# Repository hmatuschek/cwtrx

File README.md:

# Multiband QRP CW TRX based on the QCX

This repository contains all CAD files for the PCBs, documentation and 
firmware sourcecode for my small [portable multi-band QRP CW transceiver](https://dm3mat.darc.de/cw2019). 

## License
This work is licensed under a [Creative Commons Attribution-ShareAlike 4.0 International License](http://creativecommons.org/licenses/by-sa/4.0/).

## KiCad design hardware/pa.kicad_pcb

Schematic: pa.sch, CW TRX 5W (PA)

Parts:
C1, C10, C19, C23, C27, C29, C30: 100n; C_Disc_D3.0mm_W2.0mm_P2.50mm
C2: 100p; C_Disc_D3.0mm_W1.6mm_P2.50mm
C3, C16: 220p; C_Disc_D3.0mm_W2.0mm_P2.50mm
C4, C7, C17: 470p; C_Disc_D3.0mm_W2.0mm_P2.50mm
C5, C18: 820p; C_Disc_D3.0mm_W2.0mm_P2.50mm
C6, C11: 220p; C_Disc_D3.0mm_W1.6mm_P2.50mm
C8: 1n; C_Disc_D3.0mm_W2.0mm_P2.50mm
C9: 1.5n; C_Disc_D3.0mm_W2.0mm_P2.50mm
C12: 470p; C_Disc_D3.0mm_W1.6mm_P2.50mm
C13: 1n; C_Disc_D3.0mm_W1.6mm_P2.50mm
C14: 1.5n; C_Disc_D3.0mm_W1.6mm_P2.50mm
C15: 100p; C_Disc_D3.0mm_W2.0mm_P2.50mm
C20, C22, C24, C31: 100n; C_Disc_D4.7mm_W2.5mm_P5.00mm
C21: 1n; C_Disc_D4.3mm_W1.9mm_P5.00mm
C25: 1u; C_Disc_D4.3mm_W1.9mm_P5.00mm
C26: 220u; CP_Radial_D6.3mm_P2.50mm
C28: 100n; C_Disc_D4.3mm_W1.9mm_P5.00mm
D1, D2, D3, D5: 1n4148; D_T-1_P5.08mm_Horizontal
D4: 1N4001; D_DO-15_P2.54mm_Vertical_AnodeUp
D6, D7: 1n4148; D_T-1_P2.54mm_Vertical_AnodeUp
H1, H2, H3, H4: GND; MountingHole_3.2mm_M3_Pad_Via
J1: Conn_Coaxial; BNC_Amphenol_B6252HB-NPP3G-50_Horizontal
J2: FromRX; PinSocket_1x08_P2.54mm_Vertical
J3: Barrel_Jack_Switch; BarrelJack_Wuerth_6941xx301002
J6: RX-HF; PinSocket_1x02_P2.54mm_Vertical
J7: TX-HF; PinSocket_1x02_P2.54mm_Vertical
J11: RXSupply; PinSocket_1x02_P2.54mm_Vertical
K1, K2, K3, K4: G6S-2; Relay_DPDT_Omron_G6S-2
L1, L5: 330n; L_Toroid_Vertical_L10.0mm_W5.0mm_P5.08mm_Diagonal_Rev
L2, L6, L10: 480n; L_Toroid_Vertical_L10.0mm_W5.0mm_P5.08mm_Diagonal
L3, L7: 750n; L_Toroid_Vertical_L10.0mm_W5.0mm_P5.08mm_Diagonal_Rev
L4, L8, L12: 1700n; L_Toroid_Vertical_L10.0mm_W5.0mm_P5.08mm_Diagonal
L9: 330n; L_Toroid_Vertical_L10.0mm_W5.0mm_P5.08mm_Diagonal
L11: 750n; L_Toroid_Vertical_L10.0mm_W5.0mm_P5.08mm_Diagonal
L13: 100u; L_Axial_L7.0mm_D3.3mm_P10.16mm_Horizontal_Fastron_MICC
L14: 22u; L_Radial_D8.7mm_P5.00mm_Fastron_07HCP
Q1, Q2, Q3, Q10: 2N3904; TO-92_Inline_Wide
Q4, Q6, Q7, Q8, Q9, Q11: BS170; TO-92_Inline_Wide
Q5: BD140-16; TO-126-3_Horizontal_TabDown
R1, R3, R5, R11: 10k; R_Axial_DIN0207_L6.3mm_D2.5mm_P2.54mm_Vertical
R2, R4, R6, R8: 100k; R_Axial_DIN0207_L6.3mm_D2.5mm_P2.54mm_Vertical
R7: 10k; R_Axial_DIN0204_L3.6mm_D1.6mm_P7.62mm_Horizontal
R9: 470; R_Axial_DIN0204_L3.6mm_D1.6mm_P5.08mm_Horizontal
R10: 1k; R_Axial_DIN0207_L6.3mm_D2.5mm_P2.54mm_Vertical
R12: 100; R_Axial_DIN0207_L6.3mm_D2.5mm_P7.62mm_Horizontal
R13: 100; R_Axial_DIN0204_L3.6mm_D1.6mm_P5.08mm_Horizontal
R14: 4.7k; R_Axial_DIN0204_L3.6mm_D1.6mm_P5.08mm_Horizontal
R15, R16: 10k; R_Axial_DIN0204_L3.6mm_D1.6mm_P2.54mm_Vertical
T1: 8+8@FT37-43; Transformer_1P_1S_Toroid_Vertical_D10.5mm_Amidon-T37
U1: 74HCT00; DIP-14_W7.62mm_LongPads

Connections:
10m: J2.5, R1.1
20m: J2.6, R3.1
40m: J2.7, R11.1
80m: J2.8, R5.1
+5V: C28.2, J2.1, R14.1, U1.14 (VCC)
+12V: C1.2, C10.2, C19.2, C22.2, C27.2, C29.2, D1.1 (K), D2.1 (K), D3.1 (K), D5.1 (K), K1.1, K2.1, K3.1, K4.1, L13.1, R7.2
GND: C2.2, C3.2, C4.2, C5.2, C6.2, C7.2, C8.2, C9.2, C11.2, C12.2, C13.2, C14.2, C15.2, C16.2, C17.2, C18.2, C22.1, C23.1, C24.1, C26.2, C28.1, C29.1, C30.2, C31.1, D4.2 (A), D6.2 (A), D7.1 (K), H1.1, H2.1, H3.1, H4.1, J1.2 (Ext), J2.2, J3.2, J6.2, J7.2, J11.2, K1.3, K1.10, K2.3, K2.10, K3.3, K3.10, K4.3, K4.10, Q1.1 (E), Q2.1 (E), Q3.1 (E), Q6.3 (S), Q7.3 (S), Q8.3 (S), Q9.3 (S), Q10.1 (E), Q11.3 (S), R2.2, R4.2, R6.2, R8.2, R15.1, R16.1, U1.7 (GND)
KEY5V: J2.4, R13.2
LPF: C20.1, C21.2, K1.5, K2.5, K3.5, K4.5
unnamed: C2.1, K1.9, L1.1
unnamed: C3.1, K2.9, L2.1
unnamed: C4.1, K3.9, L3.1
unnamed: C5.1, K4.9, L4.1
unnamed: C6.1, L1.2, L5.1
unnamed: C7.1, L2.2, L6.1
unnamed: C8.1, L3.2, L7.1
unnamed: C9.1, L4.2, L8.1
unnamed: C11.1, L5.2, L9.1
unnamed: C12.1, L6.2, L10.1
unnamed: C13.1, L7.2, L11.1
unnamed: C14.1, L8.2, L12.1
unnamed: C15.1, K1.4, L9.2
unnamed: C16.1, K2.4, L10.2
unnamed: C17.1, K3.4, L11.2
unnamed: C18.1, K4.4, L12.2
unnamed: C20.2, T1.2 (AB)
unnamed: C21.1, Q4.1 (D), R7.1
unnamed: C23.2, C25.1, Q5.2 (C), T1.4 (SB)
unnamed: C25.2, Q5.3 (B), R9.1, R10.2
unnamed: C26.1, C31.2, L14.1, Q5.1 (E), R9.2
unnamed: C30.1, Q4.2 (G), R12.1, R16.2
unnamed: J1.1 (In), K1.8, K2.8, K3.8, K4.8
unnamed: Q1.2 (B), R1.2, R2.1
unnamed: Q2.2 (B), R3.2, R4.1
unnamed: Q3.2 (B), R5.2, R6.1
unnamed: Q8.1 (D), R10.1
unnamed: Q8.2 (G), R13.1, R15.2
unnamed: Q10.2 (B), R8.1, R11.2
unnamed: Q6.1 (D), Q7.1 (D), Q9.1 (D), Q11.1 (D), T1.1 (AA), T1.3 (SA)
unnamed: Q6.2 (G), Q7.2 (G), Q9.2 (G), Q11.2 (G), U1.3, U1.6
unnamed: U1.1, U1.2, U1.4, U1.5, U1.11
RL10M: C1.1, D1.2 (A), K1.12, Q1.3 (C)
RL20M: C10.1, D2.2 (A), K2.12, Q2.3 (C)
RL40M: C27.1, D5.2 (A), K3.12, Q10.3 (C)
RL80M: C19.1, D3.2 (A), K4.12, Q3.3 (C)
RX5V: R12.2, U1.8
RX-HF: D6.1 (K), D7.2 (A), J6.1, Q4.3 (S)
TX5V: J2.3, U1.9, U1.10, U1.13
TX-HF: J7.1, R14.2, U1.12
VCC: C24.2, D4.1 (K), J3.1, J11.1, L13.2, L14.2

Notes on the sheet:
LP 10m
LP 17m
LP 30m
LP 60m
11T@T37-6
13T@T37-6
14T@T37-2
21T@T37-2

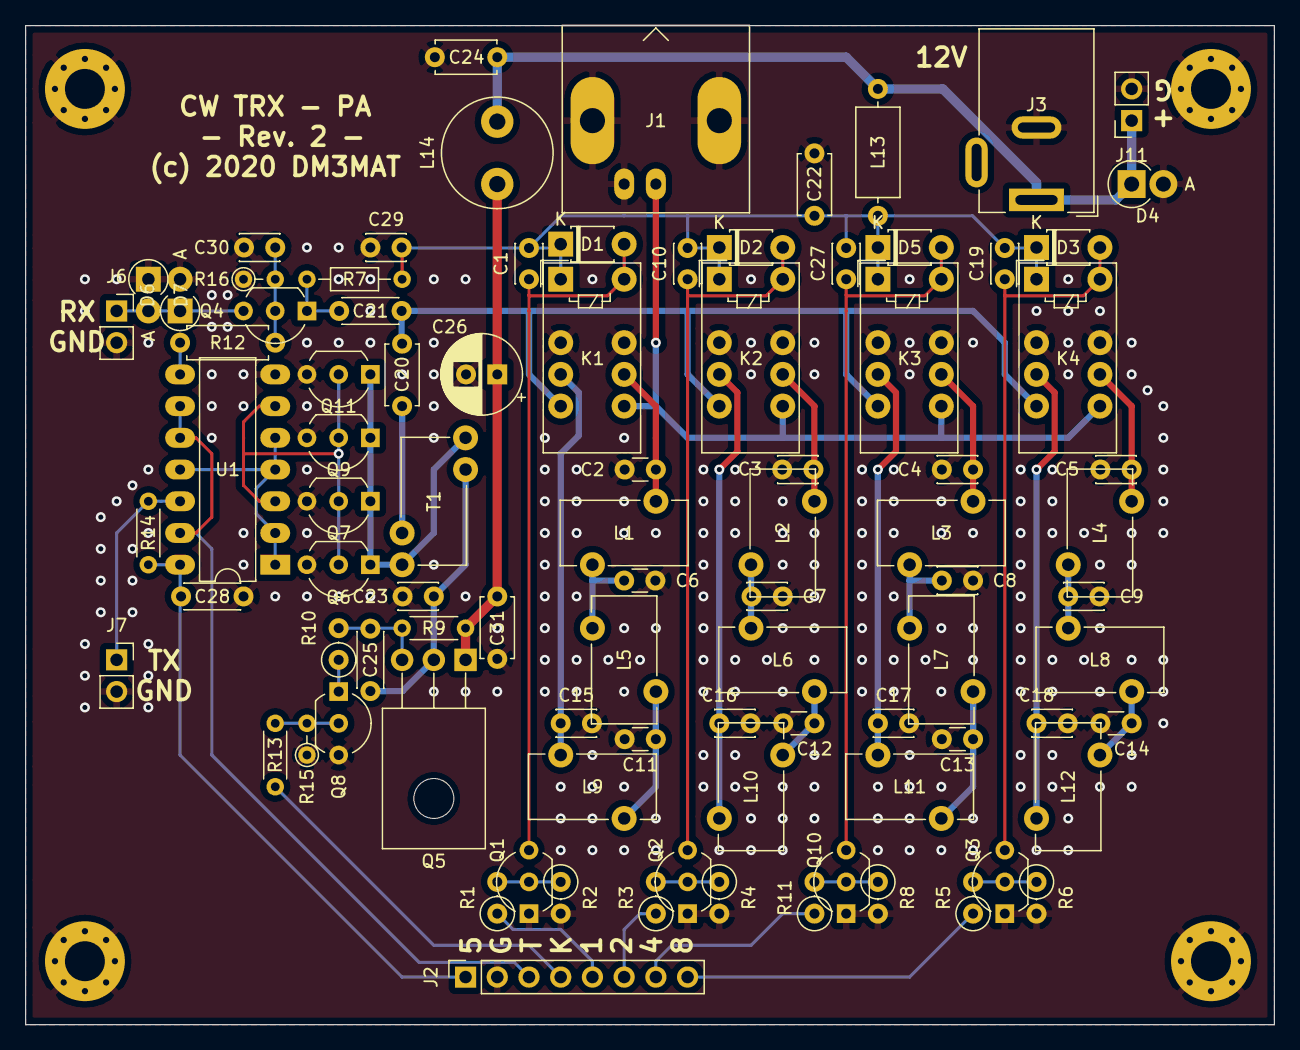
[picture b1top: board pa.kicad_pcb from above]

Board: 2 copper layers, 100.0 x 80.0 mm, 95 parts (0 on the bottom side), 50 nets.

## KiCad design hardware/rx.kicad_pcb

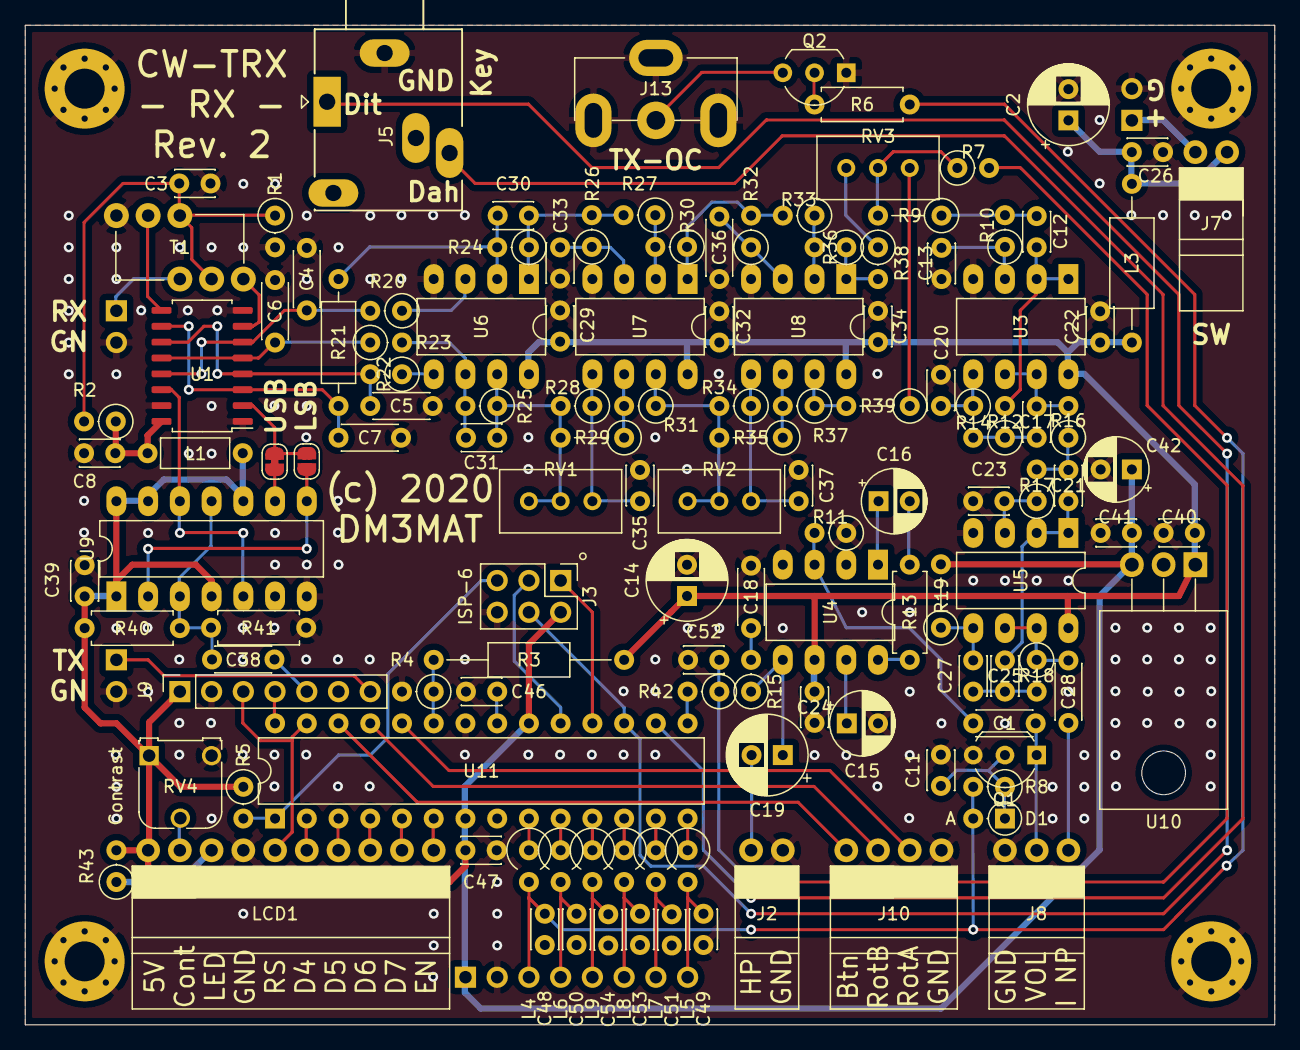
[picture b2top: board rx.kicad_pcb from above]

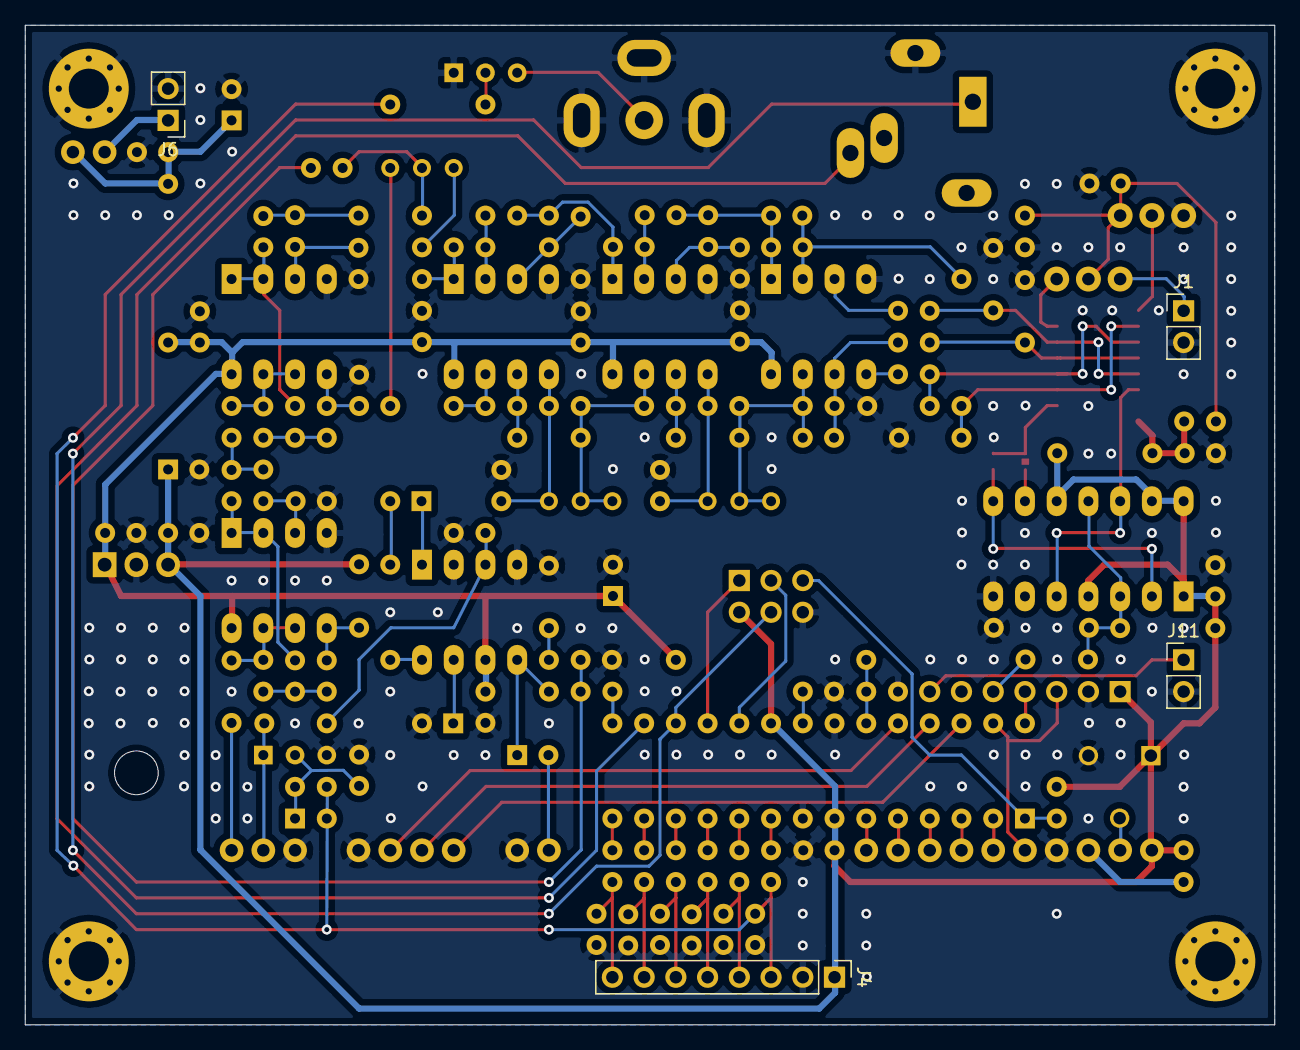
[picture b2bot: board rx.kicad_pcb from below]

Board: 2 copper layers, 100.0 x 80.0 mm, 137 parts (4 on the bottom side), 100 nets.

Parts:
C1, C28: 1u; C_Disc_D4.3mm_W1.9mm_P5.00mm
C2, C14, C19: 100u; CP_Radial_D6.3mm_P2.50mm
C3, C8, C11, C22, C24, C26, C29, C32, C34, C37, C39, C40, C41, C46, C47, C48, C49, C50, C51, C52, C53, C54: 100n; C_Disc_D3.0mm_W2.0mm_P2.50mm
C4, C5, C6, C7, C36: 470n; C_Disc_D4.3mm_W1.9mm_P5.00mm
C12, C17, C21, C33: 47n; C_Disc_D3.0mm_W2.0mm_P2.50mm
C13, C20, C23: 1n; C_Disc_D3.0mm_W2.0mm_P2.50mm
C15, C16, C42: 10u; CP_Radial_D5.0mm_P2.50mm
C18: 47n; C_Disc_D4.3mm_W1.9mm_P5.00mm
C25, C27: 3.3n; C_Disc_D3.0mm_W2.0mm_P2.50mm
C30, C31, C35: 10n; C_Disc_D3.0mm_W2.0mm_P2.50mm
C38: 100n; C_Disc_D4.3mm_W1.9mm_P5.00mm
D1: 1N4148; D_DO-35_SOD27_P2.54mm_Vertical_AnodeUp
H1, H2, H3, H4: GND; MountingHole_3.2mm_M3_Pad_Via
J1: RX-RF; PinHeader_1x02_P2.54mm_Vertical
J2: HP; Connector_BKL_1x02_P2.54mm_Horizontal
J3: AVR-ISP-6; PinHeader_2x03_P2.54mm_Vertical
J4: ToPA; PinHeader_1x08_P2.54mm_Vertical
J5: Key; Jack_3.5mm_Ledino_KB3SPRS_Horizontal
J6: Supply; PinHeader_1x02_P2.54mm_Vertical
J7: SW; Connector_BKL_1x02_P2.54mm_Horizontal
J8: 10K Log; Connector_BKL_1x03_P2.54mm_Horizontal
J9: Si5351; PinSocket_1x07_P2.54mm_Vertical
J10: ROT; Connector_BKL_1x04_P2.54mm_Horizontal
J11: TxOsc; PinHeader_1x02_P2.54mm_Vertical
J13: Conn_Coaxial; RCA_RND_205-00698_Horizontal
JP1: LSB; SolderJumper-2_P1.3mm_Open_RoundedPad1.0x1.5mm
JP2: USB; SolderJumper-2_P1.3mm_Bridged_RoundedPad1.0x1.5mm
L1: 100u; L_Axial_L5.3mm_D2.2mm_P7.62mm_Horizontal_Vishay_IM-1
L3: 100u; L_Axial_L7.0mm_D3.3mm_P12.70mm_Horizontal_Fastron_MICC
L4, L5, L6, L7, L8, L9: 100u; L_Axial_L7.0mm_D3.3mm_P2.54mm_Vertical_Fastron_MICC
LCD1: LCD; Connector_BKL_1x10_P2.54mm_Horizontal
Q1: BS170; TO-92_Inline_Wide
Q2: 2N3904; TO-92_Inline_Wide
R1, R2, R11, R18, R24, R25, R28: 10k; R_Axial_DIN0207_L6.3mm_D2.5mm_P2.54mm_Vertical
R3: 47k; R_Axial_DIN0207_L6.3mm_D2.5mm_P15.24mm_Horizontal
R4: 4.7k; R_Axial_DIN0207_L6.3mm_D2.5mm_P2.54mm_Vertical
R5: 47k; R_Axial_DIN0207_L6.3mm_D2.5mm_P2.54mm_Vertical
R6, R40, R41: 10k; R_Axial_DIN0207_L6.3mm_D2.5mm_P7.62mm_Horizontal
R7, R27, R30, R31, R33, R36, R37: 3.3k; R_Axial_DIN0207_L6.3mm_D2.5mm_P2.54mm_Vertical
R8: 120k; R_Axial_DIN0207_L6.3mm_D2.5mm_P2.54mm_Vertical
R9: 30k; R_Axial_DIN0207_L6.3mm_D2.5mm_P5.08mm_Vertical
R10: 30k; R_Axial_DIN0207_L6.3mm_D2.5mm_P2.54mm_Vertical
R12, R14: 33k; R_Axial_DIN0207_L6.3mm_D2.5mm_P2.54mm_Vertical
R13: 2.2k; R_Axial_DIN0207_L6.3mm_D2.5mm_P7.62mm_Horizontal
R15: 10; R_Axial_DIN0207_L6.3mm_D2.5mm_P2.54mm_Vertical
R16, R17: 36k; R_Axial_DIN0207_L6.3mm_D2.5mm_P2.54mm_Vertical
R19: 470k; R_Axial_DIN0207_L6.3mm_D2.5mm_P5.08mm_Vertical
R20, R22, R23: 100; R_Axial_DIN0207_L6.3mm_D2.5mm_P2.54mm_Vertical
R21: 100; R_Axial_DIN0207_L6.3mm_D2.5mm_P10.16mm_Horizontal
R26: 5.1k; R_Axial_DIN0207_L6.3mm_D2.5mm_P2.54mm_Vertical
R29, R35: 3.3k; R_Axial_DIN0207_L6.3mm_D2.5mm_P5.08mm_Vertical
R32: 4.3k; R_Axial_DIN0207_L6.3mm_D2.5mm_P2.54mm_Vertical
R34: 7.5k; R_Axial_DIN0207_L6.3mm_D2.5mm_P2.54mm_Vertical
R38, R42: 1k; R_Axial_DIN0207_L6.3mm_D2.5mm_P2.54mm_Vertical
R39: 1k; R_Axial_DIN0207_L6.3mm_D2.5mm_P5.08mm_Vertical
R43: 220; R_Axial_DIN0207_L6.3mm_D2.5mm_P2.54mm_Vertical
RV1, RV2: 50k; Potentiometer_Bourns_3296W_Vertical
RV3: 500; Potentiometer_Bourns_3296W_Vertical
RV4: 10k; Potentiometer_Runtron_RM-065_Vertical
T1: 3 x 8 @ FT37-43; Transformer_1P_2S_Toroid_Vertical_D10.5mm_Amidon-T37
U1: FST3253; SOIC-16_4.55x10.3mm_P1.27mm
U3, U5, U6, U7, U8: LM833; DIP-8_W7.62mm_LongPads
U4: LM386; DIP-8_W7.62mm_LongPads
U9: 74HC74; DIP-14_W7.62mm_LongPads
U10: L7805; TO-220-3_Horizontal_TabDown
U11: ATmega328-PU; DIP-28_W7.62mm

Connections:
10M: L9.1, U11.11
20M: L8.1, U11.12
40M: L7.1, U11.13
80M: L5.1, U11.14
+5VA: C8.1, L1.2, R2.1, U1.16
+5VD: C39.2, C41.1, C42.1, C47.1, J3.2, J4.1, J9.1, L1.1, LCD1.1, R5.1, R19.2, R40.2, R43.2, RV4.1, U9.1, U9.4, U9.10, U9.13, U9.14, U10.3, U11.7, U11.20
+12V: C14.1, C22.1, C24.1, C29.1, C32.1, C34.1, C40.1, L3.1, R3.1, U3.8, U4.6, U5.8, U6.8, U7.8, U8.8, U10.1
/Audio/HP: C19.2, J2.1
/Audio/NF: R7.1, R9.2, RV3.2
/Ctrl/10m: C54.2, J4.5, L9.2
/Ctrl/20m: C53.2, J4.6, L8.2
/Ctrl/40m: C51.2, J4.7, L7.2
/Ctrl/80m: C49.2, J4.8, L5.2
/Ctrl/SCL: J9.4, U11.28
/Ctrl/Side: C52.2, R7.2, R42.1
/Demod/I+: C4.1, R20.2, U1.6, U1.13
/Demod/I-: C7.1, R21.2, U1.3, U1.10
/Demod/Q+: C5.1, R22.2, U1.4, U1.11
/Demod/Q-: C6.1, R23.1, U1.5, U1.12
/Mixer/RF: J1.1, T1.2
/Mixer/VFO+I: U1.14, U9.5, U9.12
/Mixer/VFO+Q: JP1.2, JP2.1, U1.2
/VFO/CLK2: C38.2, J9.5
/VFO/VFO+Q: JP2.2, U9.9
/VFO/VFO-Q: JP1.1, U9.2, U9.8
Dah: J5.S, U11.16
Dit: J3.4, J5.T, U11.17
GND: C2.2, C3.2, C4.2, C5.2, C6.2, C7.2, C8.2, C11.2, C13.2, C14.2, C15.2, C18.2, C20.2, C22.2, C23.2, C24.2, C26.2, C29.2, C32.2, C33.2, C34.2, C35.1, C36.2, C37.1, C39.1, C40.2, C41.2, C42.2, C46.1, C47.2, C48.1, C49.1, C50.1, C51.1, C52.1, C53.1, C54.1, H1.1, H2.1, H3.1, H4.1, J1.2, J2.2, J3.6, J4.2, J5.G, J6.2, J8.1, J9.2, J10.4, J11.2, J13.2, LCD1.4, Q1.3, Q2.1, R1.2, R4.2, R11.1, R41.1, RV4.3, T1.1, U1.1, U1.8, U1.15, U3.4, U4.2, U4.4, U5.4, U6.4, U7.4, U8.4, U9.7, U10.2, U11.8, U11.22
KEY: L6.1, U11.10
Key: C50.2, J4.4, L6.2
LCD_CR: LCD1.2, RV4.2
LCD_D4: LCD1.6, U11.2
LCD_D5: LCD1.7, U11.3
LCD_D6: LCD1.8, U11.4
LCD_D7: LCD1.9, U11.5
LCD_EN: LCD1.10, U11.6
LCD_RS: J9.3, LCD1.5, U11.27
MISO: J3.1, U11.18
unnamed: C1.1, R11.2, U4.3
unnamed: C3.1, R1.1, R2.2, T1.4, T1.5
unnamed: C11.1, D1.1, Q1.2, R8.1
unnamed: C12.1, R9.1, R10.2
unnamed: C12.2, R12.2, U3.1, U3.2
unnamed: C13.1, R10.1, U3.3
unnamed: C15.1, U4.7
unnamed: C16.1, U4.1
unnamed: C16.2, R13.2
unnamed: C17.1, R12.1, R14.2
unnamed: C17.2, R16.2, U3.6, U3.7
unnamed: C18.1, R15.2
unnamed: C19.1, R15.1, U4.5
unnamed: C20.1, R14.1, U3.5
unnamed: C21.1, R16.1, R17.2
unnamed: C21.2, C25.1, U5.1, U5.2
unnamed: C23.1, R17.1, U5.3
unnamed: C25.2, C27.1, R18.2
unnamed: C27.2, R19.1, U5.5
unnamed: C28.2, R18.1, U5.6, U5.7
unnamed: C30.1, R24.1, R26.2, R27.2, U6.1
unnamed: C30.2, R21.1, R24.2, U6.2
unnamed: C31.1, R25.1, R28.2, R29.2, RV1.2, RV1.3, U6.7
unnamed: C31.2, R23.2, R25.2, U6.6
unnamed: C33.1, R26.1, U7.3
unnamed: C35.2, R28.1, RV1.1, U7.5
unnamed: C36.1, R32.1, U8.3
unnamed: C37.2, R34.1, RV2.1, U8.5
unnamed: C38.1, R40.1, R41.2, U9.3, U9.11
unnamed: C46.2, U11.21
unnamed: J6.1, J7.1
unnamed: J13.1, Q2.3
unnamed: LCD1.3, R43.1
unnamed: Q2.2, R6.1
unnamed: R13.1, U4.8
unnamed: R20.1, U6.3
unnamed: R22.1, U6.5
unnamed: R27.1, R30.2, U7.2
unnamed: R29.1, R31.2, U7.6
unnamed: R30.1, R32.2, R33.2, U7.1
unnamed: R31.1, R34.2, R35.2, RV2.2, RV2.3, U7.7
unnamed: R33.1, R36.2, U8.2
unnamed: R35.1, R37.2, U8.6
unnamed: R36.1, R38.2, U8.1
unnamed: R37.1, R39.2, U8.7
unnamed: R38.1, RV3.1
unnamed: R39.1, RV3.3
unnamed: T1.3, U1.9
unnamed: T1.6, U1.7
POT-A: C28.1, J8.3
POT-B: C1.2, J8.2, Q1.1
ROT-A: J10.3, U11.24
ROT-B: J10.2, U11.25
ROT-M: J10.1, U11.26
RST: J3.5, R5.2, U11.1
SCK: J3.3, U11.19
SIDE: R42.2, U11.15
TX: L4.1, U11.9
TX5V: C48.2, D1.2, J4.3, L4.2, R6.2, R8.2
TX-OSC: J9.7, J11.1
VCC: C2.1, C26.1, J7.2, L3.2
Vbat: R3.2, R4.1, U11.23

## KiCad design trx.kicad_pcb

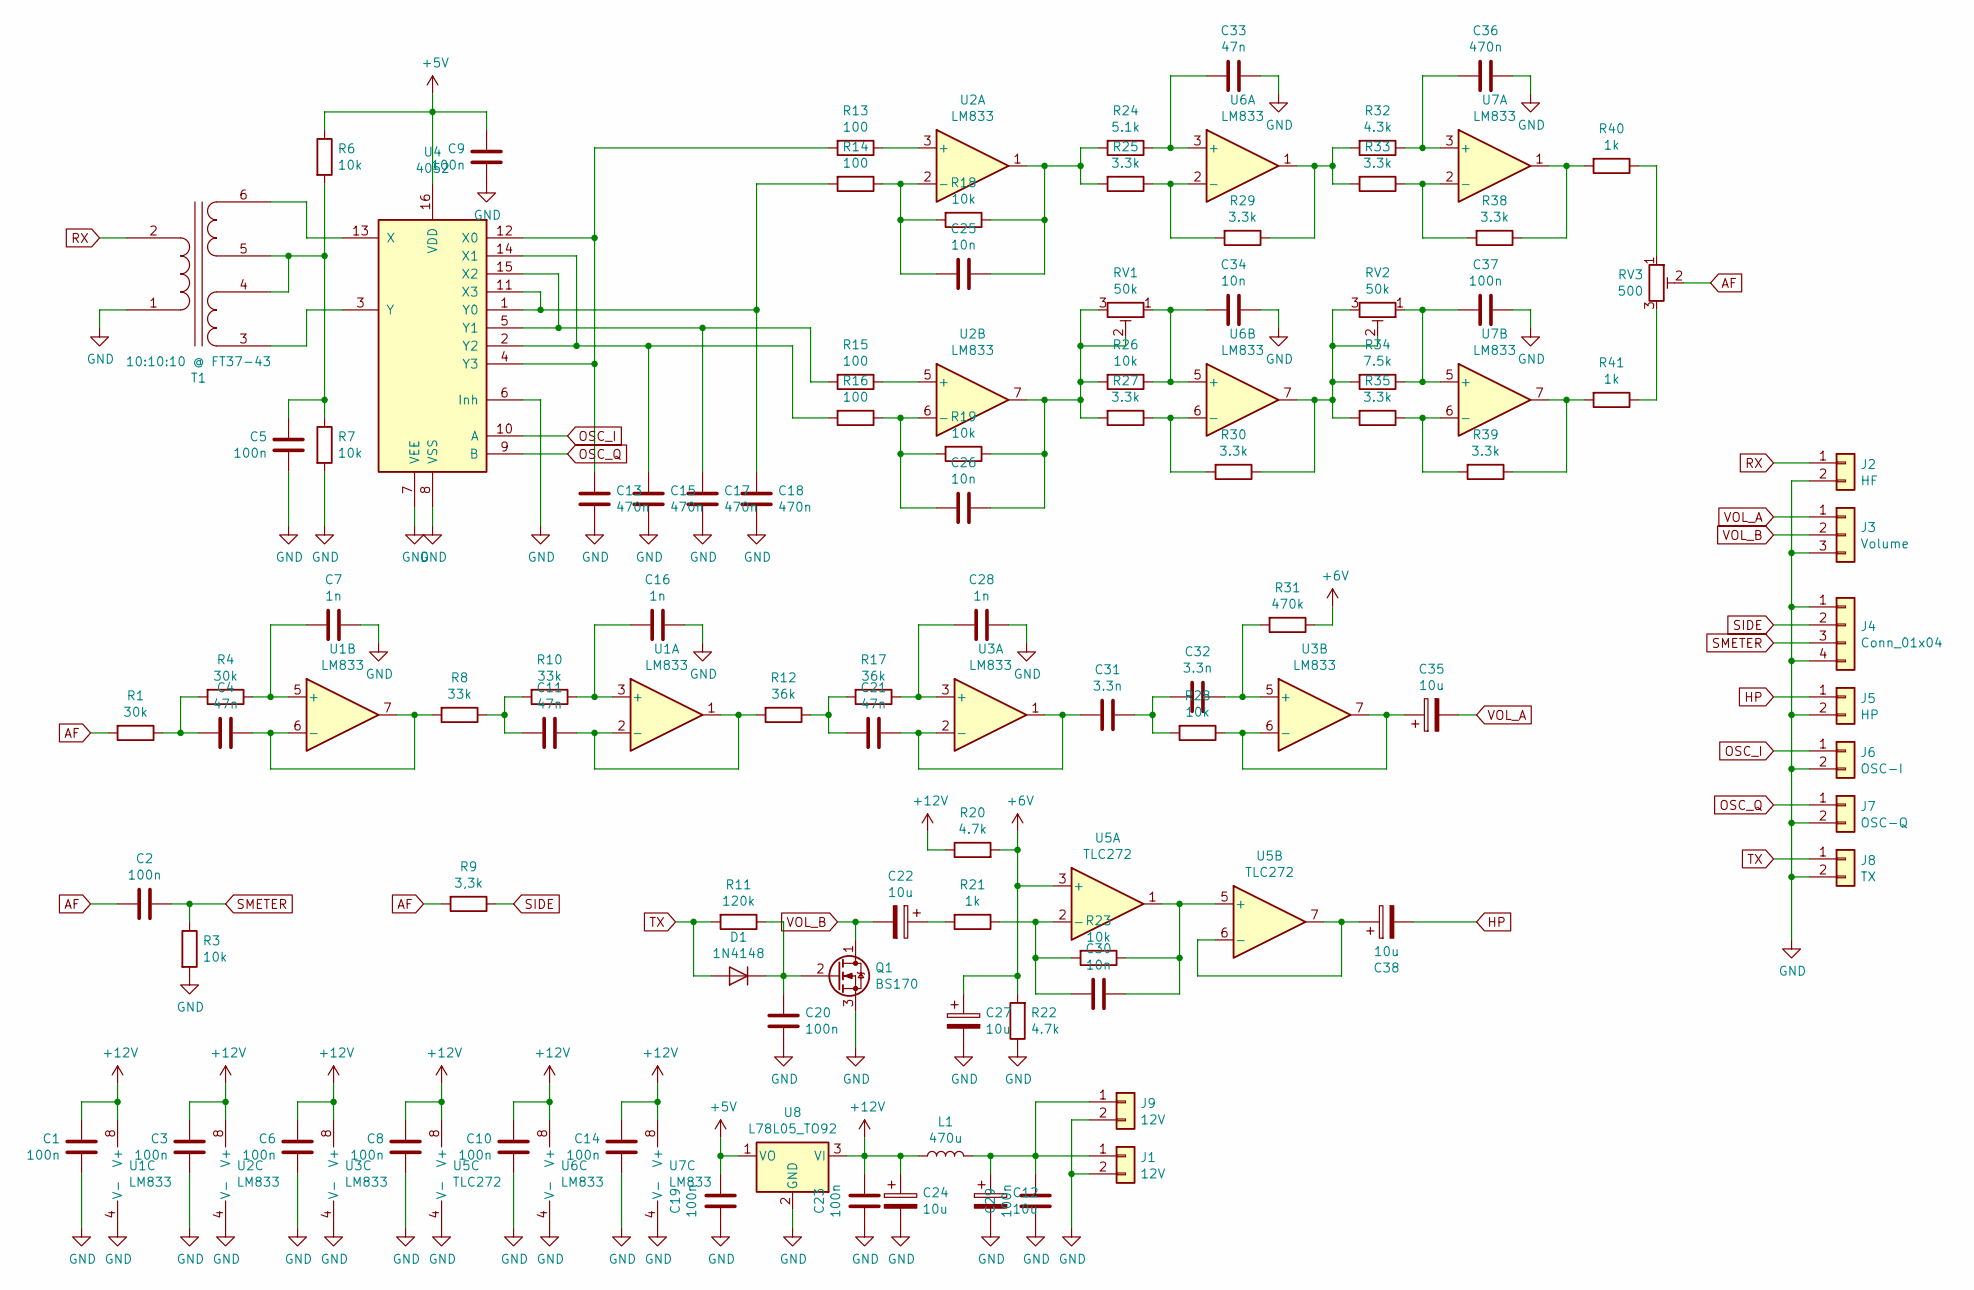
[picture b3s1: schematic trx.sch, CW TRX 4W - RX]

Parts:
C1, C3, C5, C6, C8, C10, C14, C19, C20, C23, C29: 100n; C_Disc_D3.0mm_W2.0mm_P2.50mm
C2: 100n; C_Axial_L3.8mm_D2.6mm_P7.50mm_Horizontal
C4, C11, C33: 47n; C_Disc_D3.0mm_W2.0mm_P2.50mm
C7: 1n; C_Disc_D4.3mm_W1.9mm_P5.00mm
C9, C37: 100n; C_Disc_D4.3mm_W1.9mm_P5.00mm
C12, C22, C24, C27, C35, C38: 10u; CP_Radial_D5.0mm_P2.50mm
C13: 470n; C_Disc_D4.3mm_W1.9mm_P5.00mm
C15: 470n; C_Axial_L3.8mm_D2.6mm_P10.00mm_Horizontal
C16, C28: 1n; C_Disc_D3.0mm_W2.0mm_P2.50mm
C17, C36: 470n; C_Disc_D3.0mm_W2.0mm_P2.50mm
C18: 470n; C_Axial_L3.8mm_D2.6mm_P12.50mm_Horizontal
C21: 47n; C_Disc_D4.3mm_W1.9mm_P5.00mm
C25, C26, C30: 10n; C_Disc_D3.0mm_W2.0mm_P2.50mm
C31: 3.3n; C_Axial_L3.8mm_D2.6mm_P15.00mm_Horizontal
C32: 3.3n; C_Disc_D3.0mm_W2.0mm_P2.50mm
C34: 10n; C_Disc_D4.3mm_W1.9mm_P5.00mm
D1: 1N4148; D_DO-35_SOD27_P2.54mm_Vertical_AnodeUp
J1, J9: 12V; PinHeader_1x02_P2.54mm_Vertical
J2: HF; PinHeader_1x02_P2.54mm_Vertical
J3: Volume; PinHeader_1x03_P2.54mm_Vertical
J4: Conn_01x04; PinHeader_1x04_P2.54mm_Vertical
J5: HP; PinHeader_1x02_P2.54mm_Vertical
J6: OSC-I; PinHeader_1x02_P2.54mm_Vertical
J7: OSC-Q; PinHeader_1x02_P2.54mm_Vertical
J8: TX; PinHeader_1x02_P2.54mm_Vertical
L1: 470u; L_Axial_L7.0mm_D3.3mm_P5.08mm_Vertical_Fastron_MICC
Q1: BS170; TO-92_Inline_Wide
R1, R4: 30k; R_Axial_DIN0204_L3.6mm_D1.6mm_P2.54mm_Vertical
R3, R7, R18, R19, R23: 10k; R_Axial_DIN0204_L3.6mm_D1.6mm_P2.54mm_Vertical
R6, R26, R28: 10k; R_Axial_DIN0204_L3.6mm_D1.6mm_P5.08mm_Horizontal
R8: 33k; R_Axial_DIN0207_L6.3mm_D2.5mm_P15.24mm_Horizontal
R9: 3,3k; R_Axial_DIN0204_L3.6mm_D1.6mm_P7.62mm_Horizontal
R10: 33k; R_Axial_DIN0204_L3.6mm_D1.6mm_P2.54mm_Vertical
R11: 120k; R_Axial_DIN0204_L3.6mm_D1.6mm_P2.54mm_Vertical
R12: 36k; R_Axial_DIN0204_L3.6mm_D1.6mm_P5.08mm_Horizontal
R13: 100; R_Axial_DIN0204_L3.6mm_D1.6mm_P7.62mm_Horizontal
R14, R16: 100; R_Axial_DIN0207_L6.3mm_D2.5mm_P10.16mm_Horizontal
R15: 100; R_Axial_DIN0204_L3.6mm_D1.6mm_P2.54mm_Vertical
R17: 36k; R_Axial_DIN0204_L3.6mm_D1.6mm_P2.54mm_Vertical
R20: 4.7k; R_Axial_DIN0204_L3.6mm_D1.6mm_P7.62mm_Horizontal
R21, R40: 1k; R_Axial_DIN0309_L9.0mm_D3.2mm_P12.70mm_Horizontal
R22: 4.7k; R_Axial_DIN0204_L3.6mm_D1.6mm_P2.54mm_Vertical
R24: 5.1k; R_Axial_DIN0204_L3.6mm_D1.6mm_P2.54mm_Vertical
R25, R27, R29, R30, R33, R35, R38, R39: 3.3k; R_Axial_DIN0204_L3.6mm_D1.6mm_P2.54mm_Vertical
R31: 470k; R_Axial_DIN0207_L6.3mm_D2.5mm_P15.24mm_Horizontal
R32: 4.3k; R_Axial_DIN0204_L3.6mm_D1.6mm_P2.54mm_Vertical
R34: 7.5k; R_Axial_DIN0204_L3.6mm_D1.6mm_P5.08mm_Horizontal
R41: 1k; R_Axial_DIN0204_L3.6mm_D1.6mm_P2.54mm_Vertical
RV1, RV2: 50k; Potentiometer_Bourns_3296W_Vertical
RV3: 500; Potentiometer_Bourns_3296W_Vertical
T1: 10:10:10 @ FT37-43; Transformer_1P_2S_Toroid_Vertical_D10.5mm_Amidon-T37_Wide
U1, U2, U3, U6, U7: LM833; DIP-8_W7.62mm_LongPads
U4: 4052; DIP-16_W7.62mm_LongPads
U5: TLC272; DIP-8_W7.62mm_LongPads
U8: L78L05_TO92; TO-92_Inline_Wide

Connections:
+5V: C9.2, C19.1, R6.1, U4.16 (VDD), U8.1 (VO)
+6V: C27.1, R20.2, R22.2, R31.1, U5.3 (+)
+12V: C1.2, C3.2, C6.2, C8.2, C10.2, C14.2, C23.1, C24.1, L1.1, R20.1, U1.8 (V+), U2.8 (V+), U3.8 (V+), U5.8 (V+), U6.8 (V+), U7.8 (V+), U8.3 (VI)
AF: C2.2, R1.2, R9.2, RV3.2
GND: C1.1, C3.1, C5.1, C6.1, C7.1, C8.1, C9.1, C10.1, C12.2, C13.2, C14.1, C15.2, C16.1, C17.2, C18.2, C19.2, C20.1, C23.2, C24.2, C27.2, C28.1, C29.2, C33.1, C34.1, C36.1, C37.1, J1.2, J2.2, J3.3, J4.1, J4.4, J5.2, J6.2, J7.2, J8.2, J9.2, Q1.3 (S), R3.2, R7.2, R22.1, T1.1 (AA), U1.4 (V-), U2.4 (V-), U3.4 (V-), U4.6 (Inh), U4.7 (VEE), U4.8 (VSS), U5.4 (V-), U6.4 (V-), U7.4 (V-), U8.2 (GND)
HP: C38.2, J5.1
unnamed: C4.1, R8.2, U1.6 (-), U1.7
unnamed: C4.2, R1.1, R4.2
unnamed: C5.2, R6.2, R7.1, T1.4 (SB), T1.5 (SC)
unnamed: C7.2, R4.1, U1.5 (+)
unnamed: C11.1, R12.2, U1.1, U1.2 (-)
unnamed: C11.2, R8.1, R10.2
unnamed: C12.1, C29.1, J1.1, J9.1, L1.2
unnamed: C13.1, R13.2, U4.4 (Y3), U4.12 (X0)
unnamed: C15.1, R16.2, U4.2 (Y2), U4.14 (X1)
unnamed: C16.2, R10.1, U1.3 (+)
unnamed: C17.1, R15.2, U4.5 (Y1), U4.15 (X2)
unnamed: C18.1, R14.2, U4.1 (Y0), U4.11 (X3)
unnamed: C20.2, D1.1 (K), Q1.2 (G), R11.1
unnamed: C21.1, C31.2, U3.1, U3.2 (-)
unnamed: C21.2, R12.1, R17.2
unnamed: C22.1, R21.2
unnamed: C25.1, R18.1, R24.2, R25.2, U2.1
unnamed: C25.2, R14.1, R18.2, U2.2 (-)
unnamed: C26.1, R19.1, R26.2, R27.2, RV1.2, RV1.3, U2.7
unnamed: C26.2, R16.1, R19.2, U2.6 (-)
unnamed: C28.2, R17.1, U3.3 (+)
unnamed: C30.1, R23.1, U5.1, U5.5 (+)
unnamed: C30.2, R21.1, R23.2, U5.2 (-)
unnamed: C31.1, C32.2, R28.2
unnamed: C32.1, R31.2, U3.5 (+)
unnamed: C33.2, R24.1, U6.3 (+)
unnamed: C34.2, R26.1, RV1.1, U6.5 (+)
unnamed: C35.1, R28.1, U3.6 (-), U3.7
unnamed: C36.2, R32.1, U7.3 (+)
unnamed: C37.2, R34.1, RV2.1, U7.5 (+)
unnamed: C38.1, U5.6 (-), U5.7
unnamed: R13.1, U2.3 (+)
unnamed: R15.1, U2.5 (+)
unnamed: R25.1, R29.2, U6.2 (-)
unnamed: R27.1, R30.2, U6.6 (-)
unnamed: R29.1, R32.2, R33.2, U6.1
unnamed: R30.1, R34.2, R35.2, RV2.2, RV2.3, U6.7
unnamed: R33.1, R38.2, U7.2 (-)
unnamed: R35.1, R39.2, U7.6 (-)
unnamed: R38.1, R40.2, U7.1
unnamed: R39.1, R41.2, U7.7
unnamed: R40.1, RV3.1
unnamed: R41.1, RV3.3
unnamed: T1.3 (SA), U4.3 (Y)
unnamed: T1.6 (SD), U4.13 (X)
OSC_I: J6.1, U4.10 (A)
OSC_Q: J7.1, U4.9 (B)
RX: J2.1, T1.2 (AB)
SIDE: J4.2, R9.1
SMETER: C2.1, J4.3, R3.1
TX: D1.2 (A), J8.1, R11.2
VOL_A: C35.2, J3.1
VOL_B: C22.2, J3.2, Q1.1 (D)

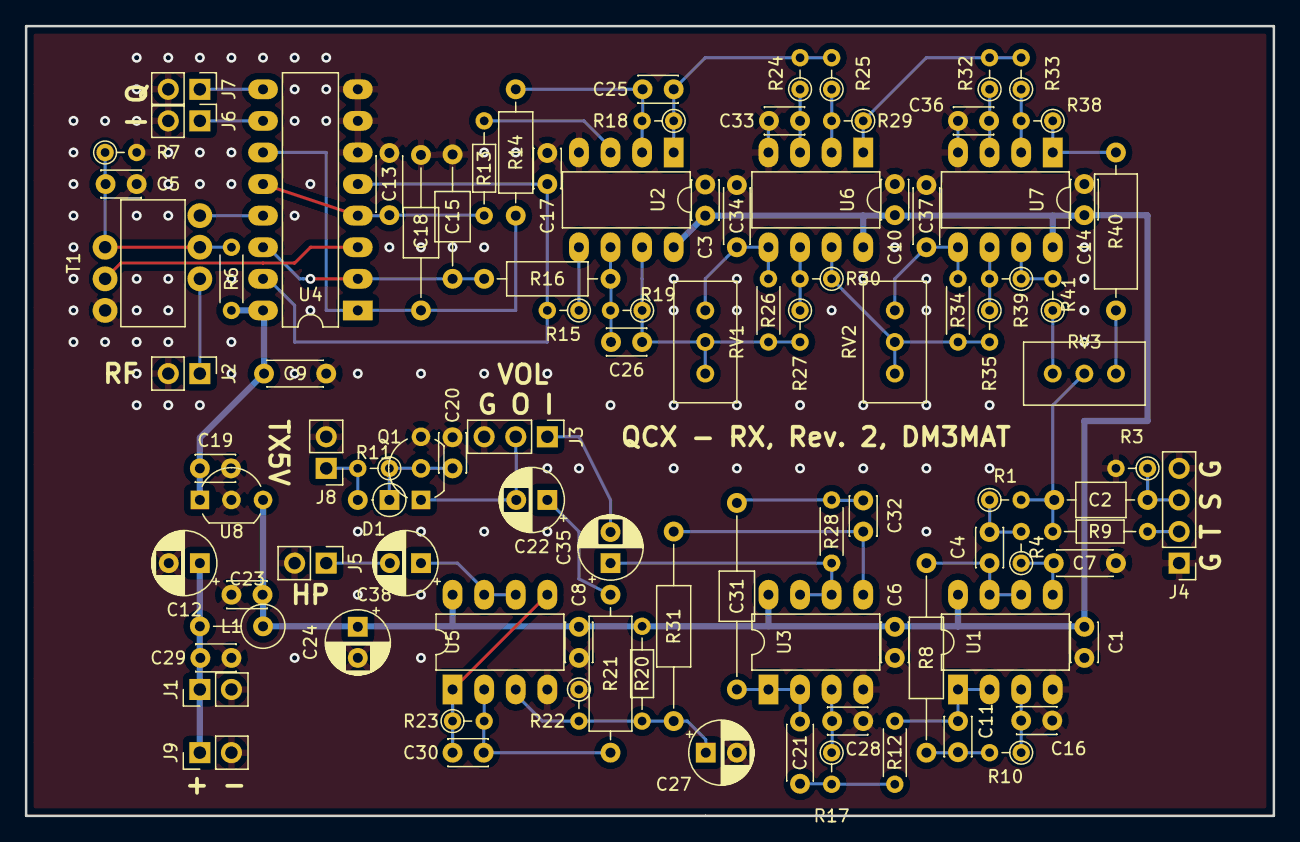
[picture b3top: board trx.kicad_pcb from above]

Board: 2 copper layers, 100.3 x 63.5 mm, 99 parts (0 on the bottom side), 59 nets.

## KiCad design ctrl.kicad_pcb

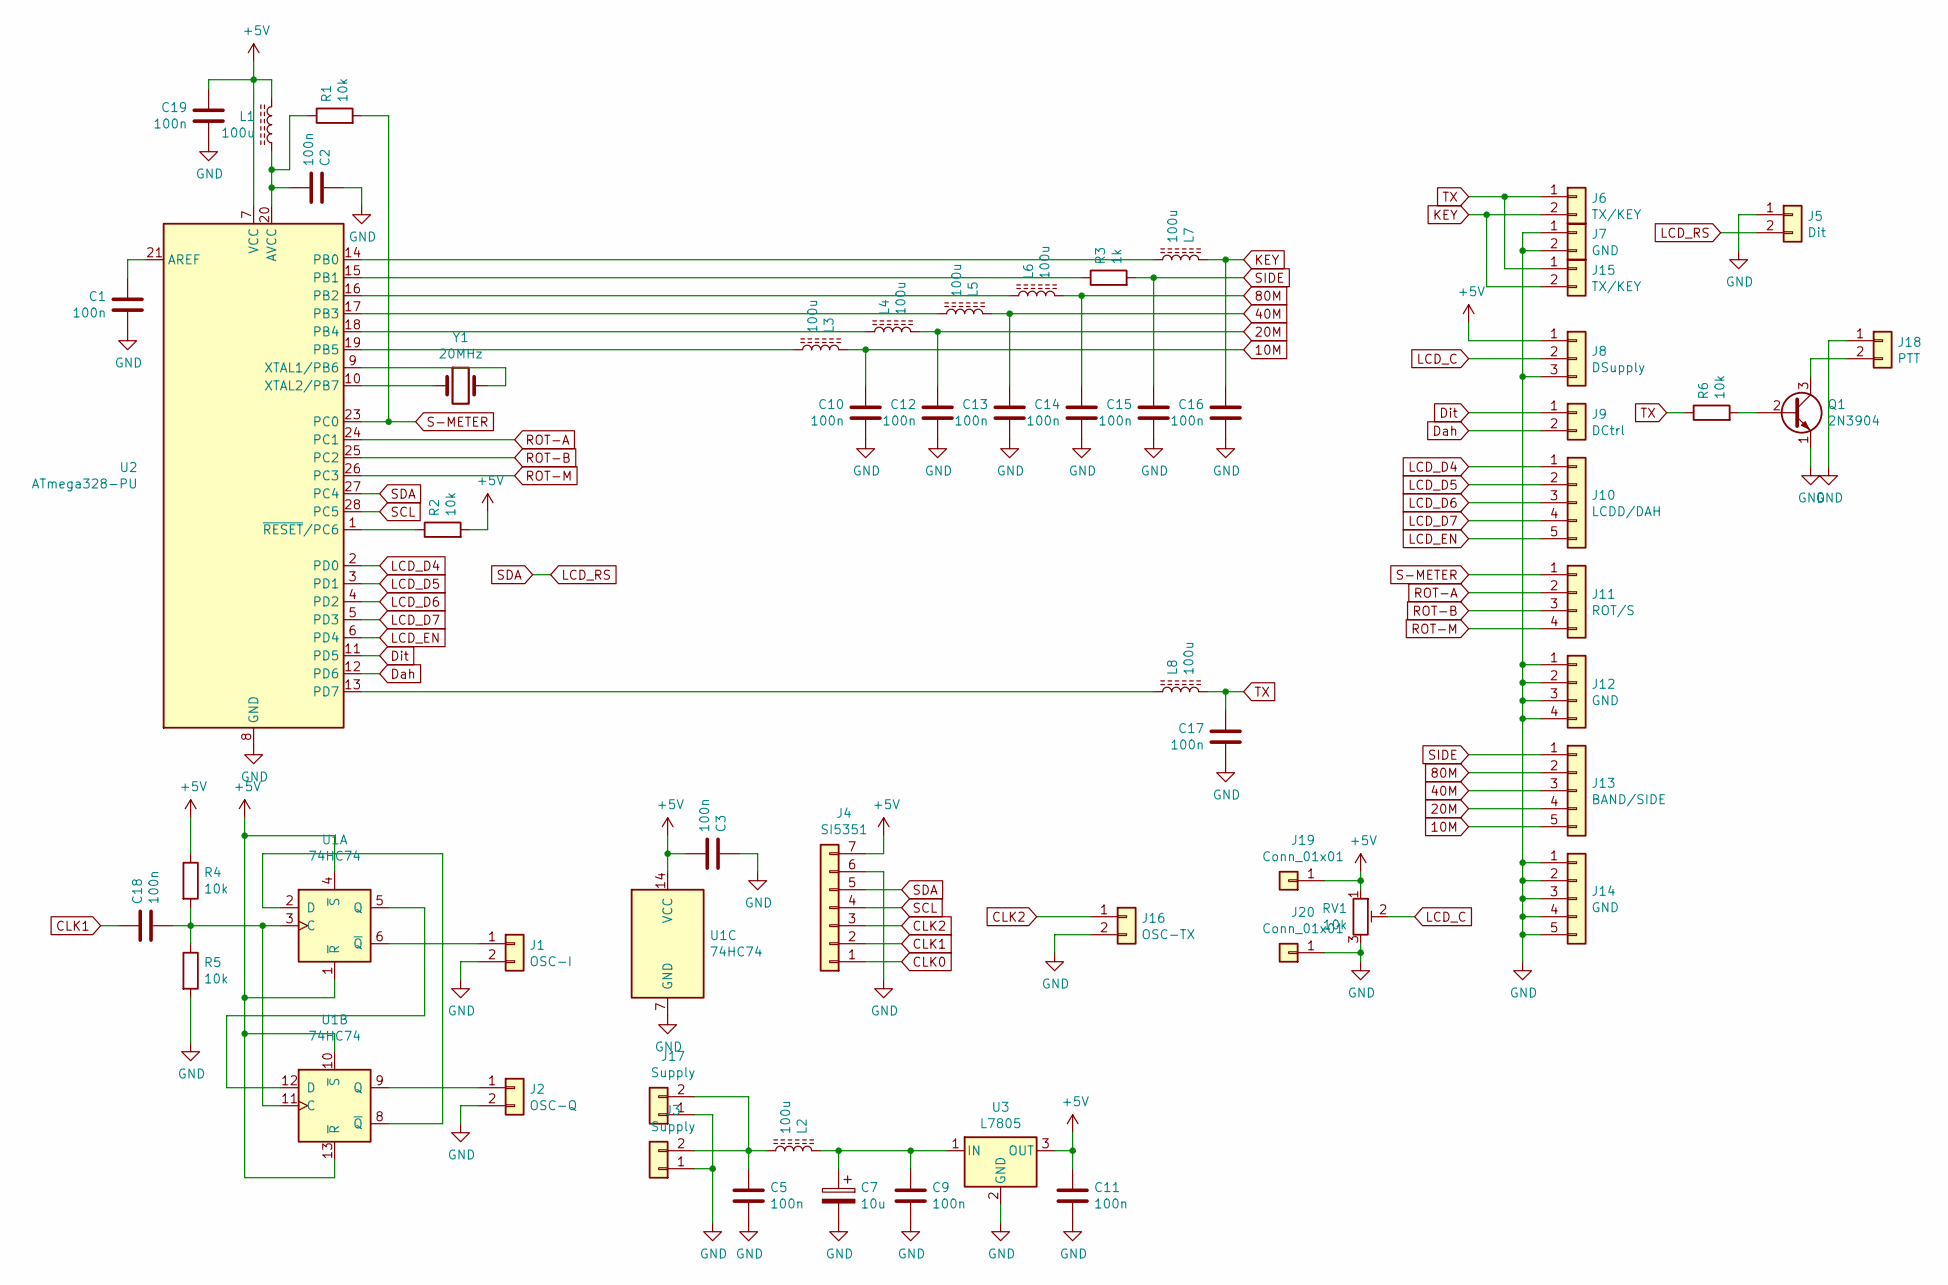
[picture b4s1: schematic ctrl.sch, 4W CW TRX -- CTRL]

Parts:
C1, C5, C9, C10, C11, C12, C13, C14, C15, C16, C17, C19: 100n; C_Disc_D3.0mm_W2.0mm_P2.50mm
C2, C3, C18: 100n; C_Disc_D4.7mm_W2.5mm_P5.00mm
C7: 10u; CP_Radial_D5.0mm_P2.50mm
J1: OSC-I; PinHeader_1x02_P2.54mm_Vertical
J2: OSC-Q; PinHeader_1x02_P2.54mm_Vertical
J3, J17: Supply; PinHeader_1x02_P2.54mm_Vertical
J4: SI5351; PinHeader_1x07_P2.54mm_Vertical
J5: Dit; PinHeader_1x02_P2.54mm_Vertical
J6, J15: TX/KEY; PinHeader_1x02_P2.54mm_Vertical
J7: GND; PinHeader_1x02_P2.54mm_Vertical
J8: DSupply; PinHeader_1x03_P2.54mm_Vertical
J9: DCtrl; PinHeader_1x02_P2.54mm_Vertical
J10: LCDD/DAH; PinHeader_1x05_P2.54mm_Vertical
J11: ROT/S; PinHeader_1x04_P2.54mm_Vertical
J12: GND; PinHeader_1x04_P2.54mm_Vertical
J13: BAND/SIDE; PinHeader_1x05_P2.54mm_Vertical
J14: GND; PinHeader_1x05_P2.54mm_Vertical
J16: OSC-TX; PinHeader_1x02_P2.54mm_Vertical
J18: PTT; PinHeader_1x02_P2.54mm_Vertical
J19, J20: Conn_01x01; PinHeader_1x01_P2.54mm_Vertical
L1: 100u; L_Axial_L5.3mm_D2.2mm_P10.16mm_Horizontal_Vishay_IM-1
L2, L3, L4, L5, L6, L7, L8: 100u; L_Axial_L7.0mm_D3.3mm_P5.08mm_Vertical_Fastron_MICC
Q1: 2N3904; TO-92_Inline_Wide
R1: 10k; R_Axial_DIN0204_L3.6mm_D1.6mm_P7.62mm_Horizontal
R2: 10k; R_Axial_DIN0207_L6.3mm_D2.5mm_P15.24mm_Horizontal
R3: 1k; R_Axial_DIN0204_L3.6mm_D1.6mm_P5.08mm_Horizontal
R4, R6: 10k; R_Axial_DIN0204_L3.6mm_D1.6mm_P2.54mm_Vertical
R5: 10k; R_Axial_DIN0204_L3.6mm_D1.6mm_P5.08mm_Horizontal
RV1: 10k; Potentiometer_Vishay_T7-YA_Single_Vertical
U1: 74HC74; DIP-14_W7.62mm_LongPads
U2: ATmega328-PU; DIP-28_W7.62mm
U3: L7805; TO-220-3_Vertical
Y1: 20MHz; Crystal_HC49-U_Vertical

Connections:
10M: C10.1, J13.5, L3.1
20M: C12.1, J13.4, L4.2
40M: C13.1, J13.3, L5.1
80M: C14.1, J13.2, L6.2
+5V: C3.2, C11.1, C19.1, J4.7, J8.1, J19.1, L1.1, R2.2, R4.1, RV1.1, U1.1 (~R), U1.4 (~S), U1.10 (~S), U1.13 (~R), U1.14 (VCC), U2.7 (VCC), U3.3 (OUT)
CLK1: C18.1, J4.2
CLK2: J4.3, J16.1
Dah: J9.2, U2.12 (PD6)
Dit: J9.1, U2.11 (PD5)
GND: C1.2, C2.1, C3.1, C5.2, C7.2, C9.2, C10.2, C11.2, C12.2, C13.2, C14.2, C15.2, C16.2, C17.2, C19.2, J1.2, J2.2, J3.1, J4.6, J5.1, J7.1, J7.2, J8.3, J12.1, J12.2, J12.3, J12.4, J14.1, J14.2, J14.3, J14.4, J14.5, J16.2, J17.1, J18.1, J20.1, Q1.1 (E), R5.2, RV1.3, U1.7 (GND), U2.8 (GND), U2.22 (GND), U3.2 (GND)
KEY: C16.1, J6.2, J15.2, L7.1
LCD_C: J8.2, RV1.2
LCD_D4: J10.1, U2.2 (PD0)
LCD_D5: J10.2, U2.3 (PD1)
LCD_D6: J10.3, U2.4 (PD2)
LCD_D7: J10.4, U2.5 (PD3)
LCD_EN: J10.5, U2.6 (PD4)
LCD_RS: J4.5, J5.2, U2.27 (PC4)
unnamed: C1.1, U2.21 (AREF)
unnamed: C2.2, L1.2, R1.1, U2.20 (AVCC)
unnamed: C5.1, J3.2, J17.2, L2.2
unnamed: C7.1, C9.1, L2.1, U3.1 (IN)
unnamed: C18.2, R4.2, R5.1, U1.3 (C), U1.11 (C)
unnamed: J1.1, U1.6 (~Q)
unnamed: J2.1, U1.9 (Q)
unnamed: J18.2, Q1.3 (C)
unnamed: L3.2, U2.19 (PB5)
unnamed: L4.1, U2.18 (PB4)
unnamed: L5.2, U2.17 (PB3)
unnamed: L6.1, U2.16 (PB2)
unnamed: L7.2, U2.14 (PB0)
unnamed: L8.1, U2.13 (PD7)
unnamed: Q1.2 (B), R6.2
unnamed: R2.1, U2.1 (~RESET~/PC6)
unnamed: R3.1, U2.15 (PB1)
unnamed: U1.2 (D), U1.8 (~Q)
unnamed: U1.5 (Q), U1.12 (D)
unnamed: U2.9 (XTAL1/PB6), Y1.2
unnamed: U2.10 (XTAL2/PB7), Y1.1
ROT-A: J11.2, U2.24 (PC1)
ROT-B: J11.3, U2.25 (PC2)
ROT-M: J11.4, U2.26 (PC3)
S-METER: J11.1, R1.2, U2.23 (PC0)
SCL: J4.4, U2.28 (PC5)
SIDE: C15.1, J13.1, R3.2
TX: C17.1, J6.1, J15.1, L8.2, R6.1

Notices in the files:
hardware/pa.kicad_pcb:
(c) 2020 DM3MAT
